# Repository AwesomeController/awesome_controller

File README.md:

Awesome Controller
==================

This is the official repository for the Awesome Controller firmware, which runs on the
Arduino platform.

The various branches in this repository represent different steps in the evolution of
the software.

Running the code
========
1. Get yourself an Arduino. http://arduino.cc/en/Main/Buy
2. Get a USB host shield and attach it to your Ardiuno. https://www.sparkfun.com/products/9947?
3. Acquire a cheap bluetooth dongle, such as http://www.amazon.com/Bluetooth-USB-Micro-Adapter-Dongle/dp/B001EBE1LI
4. Create a raw dongle for the console that you want to use. A raw dongle is the console end of a controller cord.
You'll need to cut open the cord and expose the wires so that they can be connected directly to the arduino.
You could use a controller you already own, but there are other options if this is too great a sacrifice.
You could buy a cheap used or 3rd party controller from your local video game store.
There are also controller extension cords that can be purchased online or in stores. Here is an example: http://www.amazon.com/Extension-Cable-BRAND-Original-Nintendo/dp/B000NO4X10
5. Install the Arduino environment/IDE: http://arduino.cc/en/Main/Software
6. Open the awesome_controller.ino project file in the Arduino IDE
7. DONGLE WIRING
8. Load and run the code on your Arduino!
9. The software should detect which game console it is connected to automatically, and you can hopefully begin playing!

Hardware Schematics
========

In the "eagle" directory you will find files for use with EAGLE, a software suite for printed circuit board design.
These are unfinished, but will be used if we have our own circuit boards printed.

Running Tests
=============
The following instructions work for running the high-level
tests on a Macbook Pro:

* Dependencies
  * Requires Ruby 1.9+
  * brew install cmake (linking failed for me, so I had to `brew link cmake` afterwards)
  * gem install ffi

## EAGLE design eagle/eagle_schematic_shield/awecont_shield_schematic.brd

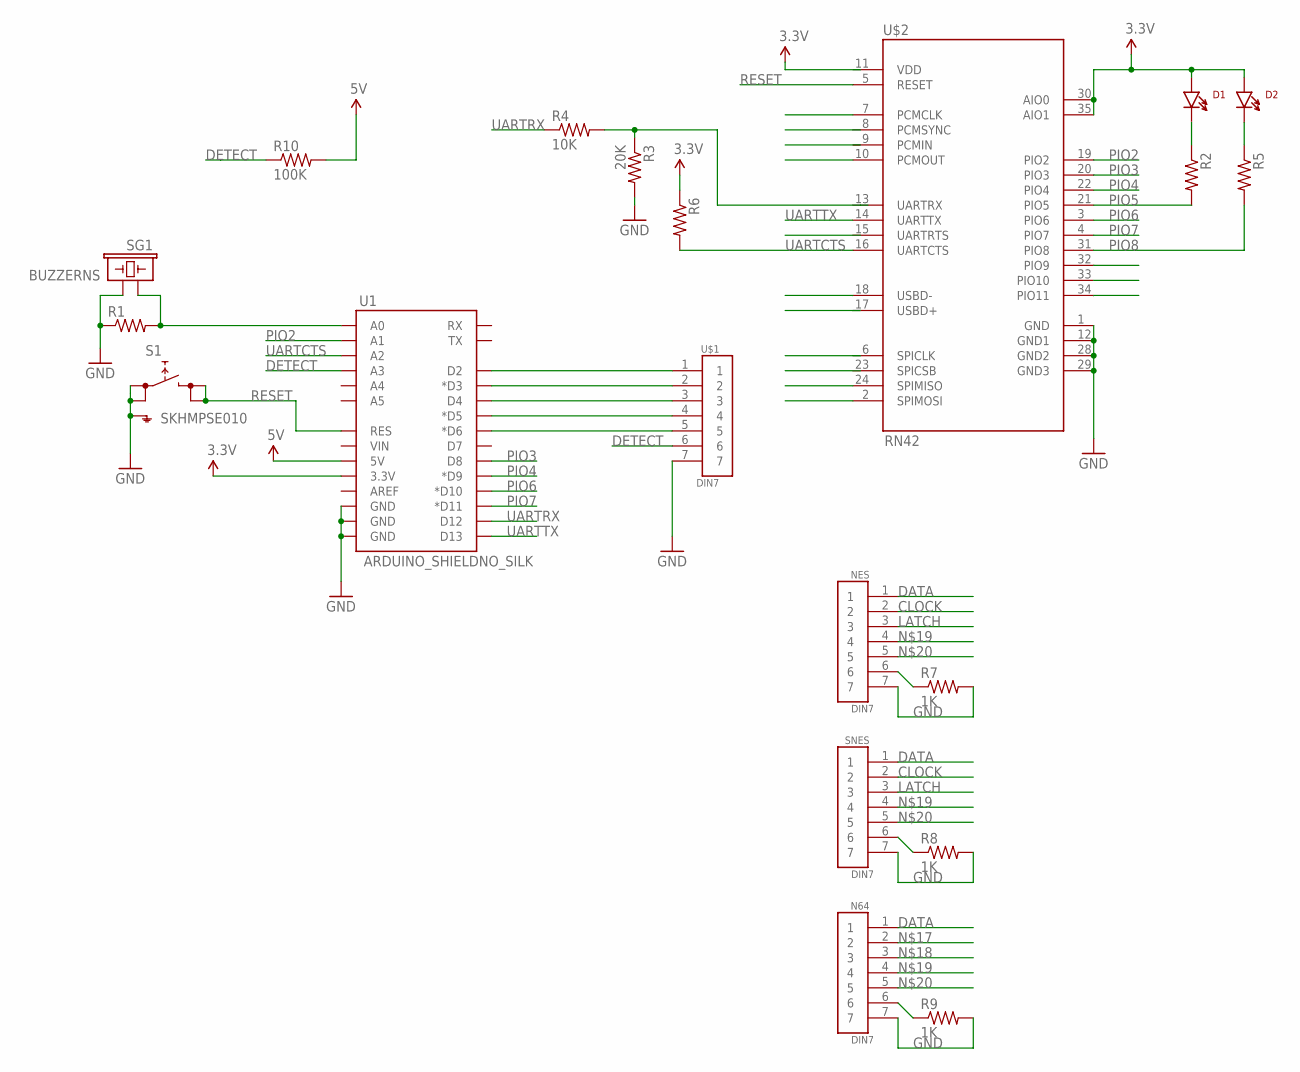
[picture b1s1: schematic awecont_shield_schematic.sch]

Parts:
D1, D2: LTE-302
N64: DIN7
NES: DIN7
R1, R2, R5, R6: RESISTORAXIAL-0.3; AXIAL-0.3
R3: 20K; AXIAL-0.3
R4: 10K; AXIAL-0.3
R7, R8, R9: 1K; AXIAL-0.3
R10: 100K; AXIAL-0.3
S1: SKHMPSE010; SKHMPXE010
SG1: BUZZERNS; BUZZER-12MM-NS
SNES: DIN7
U1: ARDUINO_SHIELDNO_SILK; DUEMILANOVE_VIAS
U$1: DIN7
U$2: RN42

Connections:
3.3V: D1.A, D2.A, R6.P$1 (1), U1.3.3V, U$2.30 (AIO0), U$2.35 (AIO1)
5V: R10.P$2 (2), U1.5V
CLOCK: NES.2, SNES.2
DATA: N64.1, NES.1, SNES.1
DETECT: R10.P$1 (1), U1.A3, U$1.6
GND: N64.7, NES.7, R1.P$1 (1), R3.P$2 (2), R7.P$2 (2), R8.P$2 (2), R9.P$2 (2), S1.1 (1.1), S1.2 (1.2), S1.5 (SH), SG1.- (2), SNES.7, U1.GND@0 (GND), U1.GND@1 (GND), U1.GND@2 (GND), U$1.7, U$2.1 (GND), U$2.12 (GND1), U$2.28 (GND2), U$2.29 (GND3)
LATCH: NES.3, SNES.3
unnamed: U1.D2, U$1.1
unnamed: U1.D3 (*D3), U$1.2
unnamed: U1.D4, U$1.3
unnamed: U1.D5 (*D5), U$1.4
unnamed: U1.D6 (*D6), U$1.5
unnamed: NES.6, R7.P$1 (1)
unnamed: R1.P$2 (2), SG1.+ (1), U1.A0
unnamed: D1.C, R2.P$1 (1)
unnamed: R8.P$1 (1), SNES.6
unnamed: N64.6, R9.P$1 (1)
unnamed: N64.3, R3.P$1 (1), R4.P$2 (2)
unnamed: N64.4, NES.4, SNES.4
unnamed: N64.5, NES.5, SNES.5
unnamed: D2.C, R5.P$1 (1)
PIO2: U1.A1, U$2.19 (PIO2)
PIO3: U1.D8, U$2.20 (PIO3)
PIO4: U1.D9 (*D9), U$2.22 (PIO4)
PIO5: R2.P$2 (2), U$2.21 (PIO5)
PIO6: U1.D10 (*D10), U$2.3 (PIO6)
PIO7: U1.D11 (*D11), U$2.4 (PIO7)
PIO8: R5.P$2 (2), U$2.31 (PIO8)
PIO9: U$2.32 (PIO9)
PIO10: U$2.33 (PIO10)
PIO11: U$2.34 (PIO11)
RESET: S1.3 (2.1), S1.4 (2.2), U1.RES, U$2.5 (RESET)
UARTCTS: R6.P$2 (2), U1.A2, U$2.16 (UARTCTS)
UARTRX: R4.P$1 (1), U1.D12
UARTTX: U1.D13, U$2.14 (UARTTX)

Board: 2 copper layers, 20 parts (0 on the bottom side), 32 nets, no tracks yet.

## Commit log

2011-11-19 Initial commit.
2011-11-19 Read button presses off of SNES controller for testing.
2011-11-19 all brokengit add .
2011-11-19 ready to send a bunch of A A A A
2011-11-19 we have a kicker - repeatably hitting A success
2011-11-19 Get ps3_usb compiling.
2011-11-19 Call SPI.begin().
2011-11-19 Read all buttons and print them out when they change.
2011-11-19 Switched pin configs to #define's
2011-11-20 Finish porting ps3_usb branch. Handle B button correctly.
2011-11-20 Moved in some bluetooth debugging with compile errors
2011-11-20 ww: Added bluetooth dongle configuration analysis
2011-11-20 ww: pulled in most of the blueutils sketch for pairing with the wii via bluetooth
    Copied over most of the code and integrated it in to the main event loop. Still need to fix some conflicts with the ps3_usb library
2011-11-20 ww: Renamed ep_records to fix global namespace collision
2011-11-20 ww: code cleanup, comments and better naming
2011-11-20 More debugging statements and refactoring
2011-11-20 added code to run NES
2011-11-20 Readd missing SNES buttons.
2011-11-21 Working Wiimote code for NES.
2011-12-03 Update dependencies and file extension for Arduino 1.0.
2011-12-03 Remove unneeded file.
2011-12-03 Some simple reformatting.
2011-12-03 Set up #ifdefs.
2011-12-03 Re-add PS3 USB handling code.
2011-12-03 Refactor to split out PS3 and Wii USB into one line.
2011-12-03 Get both PS3 and Wii working.
2011-12-04 Remove #ifdefs from main file.
2011-12-06 Add TODO list.
2011-12-06 Set Wiimote to inquiry mode.
2011-12-06 Get debugging statements working in Wiiremote library.
2011-12-06 Move USB + Bluetooth stuff into another file.
    Also change includes.
2011-12-06 Rename the WiiRemote class to BluetoothUsbHostHandler.
    Have already renamed the file, just renaming the actual text.
2011-12-06 Create the WiiController class.
2011-12-06 Move buttons into WiiRemote class.
2011-12-06 Add more to TODO.
2011-12-11 Merged in some of the n64 spikey branch using defines
    Worked one time like magic and then didn't. We blame hardware
2011-12-13 Remove vim file information.
2011-12-13 Rename macros to be a little more verbose.
2011-12-13 Refactor to split out NES and SNES.
2011-12-13 Whitespace-only changes.
    Like a good coder, separating out these commits. Also,
    do not use tabs! Four spaces, please.
2011-12-13 Removed a print statement in the interrupt handler
    Turns out... not a good idea.
2011-12-13 Move N64 code to different file.
    We are not entirely happy with this solution. Would be nice to have
    the interrupt functions be part of the N64 class, but not sure that
    this is possible when using C++.
2011-12-13 N64 code merged with bluetooth code.
    Still sending just A button presses.
2011-12-23 Read N64 works with Bluetooth. (We think)
2011-12-23 I think sending works.
    Now to remove Serial.printlns.
2011-12-23 Remove print statements. Also, mess with timing.
2011-12-29 N64 interrupt refactoring. Made interrupt handler more performant. Made A, B, Z, Start, and D-pad work.
2011-12-29 Add sensible button mapping from WiiController to N64.
2011-12-29 Make WiiRemote B button into N64 Z button. Rename A and B to 1 and 2, and Start to Plus.
2011-12-29 Re-enable PS3 via wired connection.
    Conflicts:
    awesome_controller.ino
2011-12-29 Move back to attachInterrupt to fix issue with ISR double-definition.
2011-12-29 Get on the PS3/NES combination of things.
2011-12-30 I think it might have been working.
2011-12-30 Fixed double interrupt on latch bug.
    Clearing latch at the end of the interrupt handler.
2011-12-30 Refactor exit of ISR for NES.
2011-12-30 Set NES data pin generally low outside of handler.
2011-12-30 detect extension controller, initialize them
2011-12-30 Ensure speed is not an issue in the ISR.
    We are now handling twice as much in the NES ISR and want to ensure that
    we are still able to process the NES stuff correctly.
2011-12-30 Refactor into NES system object.
    Tested thoroughly (with Dr. Mario matches.)
2011-12-30 Clatch signal working for one player
2011-12-30 Keep local copy of WiiController for callbacks in BluetoothUSBHostHandler.
2011-12-30 Handle classic controller left stick X.
2011-12-31 Recode NES a bit, and introduce branch timeouts.
2011-12-31 Map the rest of the classic controller buttons as a first pass.
2012-01-28 A spike in a new project.
2012-01-28 Added cmake submodules
2012-01-28 Restructured the project to be more awesome.
2012-01-28 Another spike.
2012-01-29 Add some debugging information to RN-42 interface spike.
2012-01-29 Set the device to be in command mode for any length of time after boot.
2012-01-29 Try to perform inquiry.
2012-01-29 Send inquiry mode correctly from Arduino.
2012-03-03 added awesome controller shield schematic eagle files
2012-03-03 most of the connections finished in the schematic the way I understand the rn42 to work. Need to figure out wiring routing on pcb layout
2012-03-05 renamed shield folder and added combined uno and ac folder for schematic
2012-03-05 added usb host and edited the uno schematic - working on combining these
2012-03-18 Basic handling of system up and down.
2012-03-18 Add down action for systems.
2012-03-18 Test shutting off N64 and turning back on.
2012-03-18 Whitespace change.
2012-03-18 Cleaning up a bit and testing.
2012-03-25 added dongle circuits to schematic
2012-03-25 Detect system via analog read of resisted voltage.
2012-03-25 NES mode only (for debugging.)
2012-03-25 at: only connect to Wii devices.
2012-03-26 added more detail to the schematic - mostly cleaning it up
2012-04-20 Some print statement cleanup.
2012-04-20 Remove TODO file (we use a different tracking system now.)
2012-04-21 Get the program working again.
    Some sort of strange interrupt / flushing / printing issue is going on
    right now. This commit mostly "fixes" it, but we need to investigate
    further.
2012-04-26 Move Eagle files into eagle subdirectory.
2012-04-26 Move Arduino firmware files into awesome_controller subdirectory.
2012-04-26 Add bluez_arduino submodule.
2012-04-26 Add wiiuse_arduino submodule.
2012-04-26 Add readme.
2012-04-26 Add rake task to test building wiiuse.
2012-04-26 Add a smoke test to ensure that WiiUse built successfully.
2012-04-26 Update readme to include Ruby library dependencies.
2012-04-26 Clarify licenses in all files.
2012-05-24 Add Rake task to copy all .c, .h, and .ino files to an awesome_controller directory.
2012-10-09 Update README with some basic instructions
2012-10-09 Fix invisible step.
2012-10-09 Add section on EAGLE schematics.
2012-10-16 Update README.md
    Add step for acquiring a 'raw' dongle.

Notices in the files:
parts and their libraries:
SparkFun-Boards: Licensing: CC v3.0 Share-Alike You are welcome to use this library for commercial purposes.
